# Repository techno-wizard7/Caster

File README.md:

# Caster
Smartwatch-esqe remote controller and communicator

This device is made to be in many ways, an arduino-based custom wrist mounted version of the Flipper-Zero with built-in LoRa, with a few key differences TBD in development. Additionally there will be a default loRa messaging app, based on Bobricus's [Armachat](https://github.com/bobricius/armachat). 

This project is still deep in alpha, and is subject to change rapidly. Contributions not accepted at this time.

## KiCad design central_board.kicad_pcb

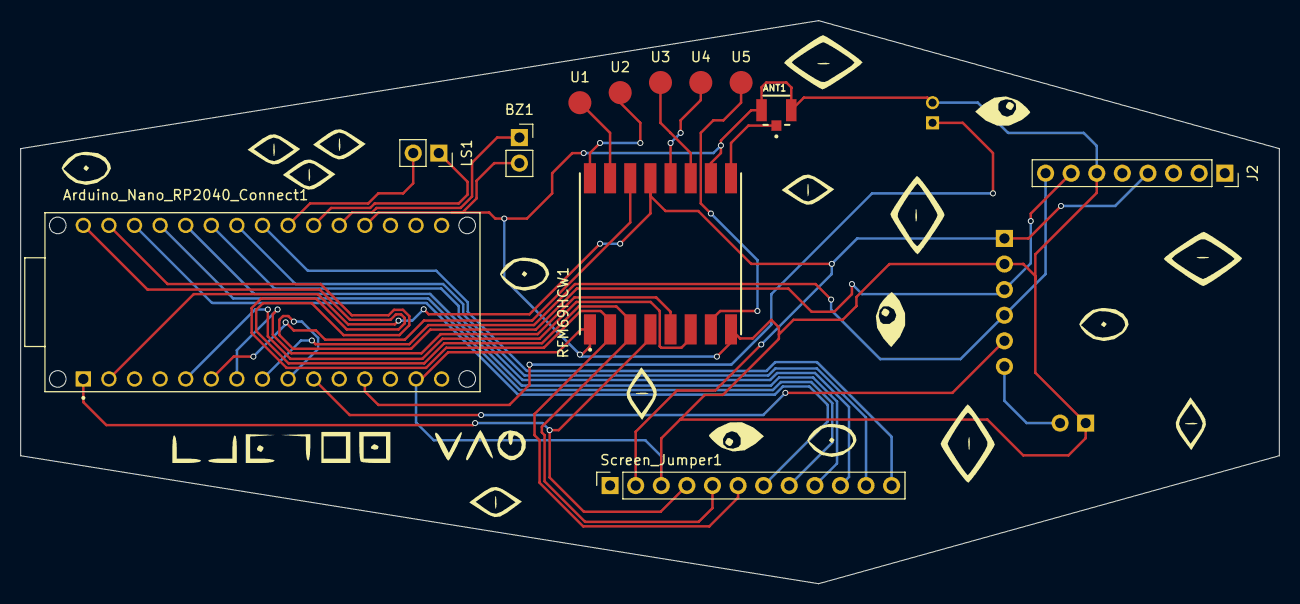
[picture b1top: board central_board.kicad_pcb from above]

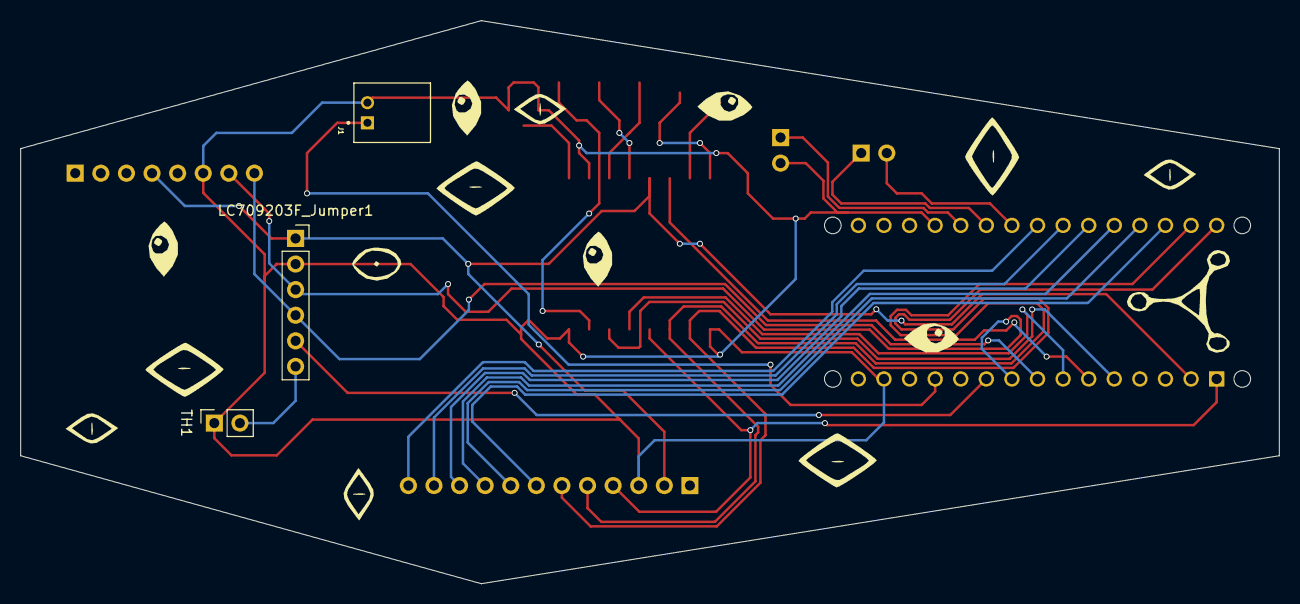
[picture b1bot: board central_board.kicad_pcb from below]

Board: 2 copper layers, 124.9 x 55.9 mm, 15 parts (3 on the bottom side), 23 nets.

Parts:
ANT1: RSP-122811-01; SAMTEC_RSP-122811-01
Arduino_Nano_RP2040_Connect1: ABX00053; MODULE_ABX00053
BZ1: Buzzer; PinSocket_1x02_P2.54mm_Vertical
J1: S2B-PH-K-S(LF)(SN); JST_S2B-PH-K-S(LF)(SN)
J2: Conn_01x08_Male; PinSocket_1x08_P2.54mm_Vertical
LC709203F_Jumper1: Conn_01x06; PinSocket_1x06_P2.54mm_Vertical
LS1: Speaker; PinSocket_1x02_P2.54mm_Vertical
RFM69HCW1: COM-13909; MOD_COM-13909
Screen_Jumper1: Conn_01x12; PinSocket_1x12_P2.54mm_Vertical
TH1: Thermistor; PinSocket_1x02_P2.54mm_Vertical
U1, U2, U3, U4, U5: Single_Jumper; JUMPERPAD

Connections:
+3V3: Arduino_Nano_RP2040_Connect1.2 (+3V3), J2.4, LC709203F_Jumper1.1, RFM69HCW1.13 (3.3V), Screen_Jumper1.2
AUD_OUT: Arduino_Nano_RP2040_Connect1.22 (D4/GPIO26), LS1.2
Aud_IN: Arduino_Nano_RP2040_Connect1.21 (D3/GPIO15), LS1.1
BUZZ: Arduino_Nano_RP2040_Connect1.20 (D2/GPIO25), BZ1.1 (-)
Bat_INT: Arduino_Nano_RP2040_Connect1.10 (A6), LC709203F_Jumper1.5
CIPO: Arduino_Nano_RP2040_Connect1.30 (D12/GPIO4/CIPO), RFM69HCW1.2 (MISO), Screen_Jumper1.6
COPI: Arduino_Nano_RP2040_Connect1.29 (D11/GPIO7/COPI), RFM69HCW1.3 (MOSI), Screen_Jumper1.5
DC: Arduino_Nano_RP2040_Connect1.26 (D8/GPIO20), Screen_Jumper1.9
GND: ANT1.G1, ANT1.G2, Arduino_Nano_RP2040_Connect1.14 (GND), Arduino_Nano_RP2040_Connect1.19 (GND), BZ1.2 (+), J1.2, J2.6, LC709203F_Jumper1.2, RFM69HCW1.1 (GND), RFM69HCW1.8 (GND), RFM69HCW1.10 (GND), Screen_Jumper1.3, TH1.1
LORA_CS: Arduino_Nano_RP2040_Connect1.7 (A3/GPIO29), RFM69HCW1.5 (NSS)
LORA_INT: Arduino_Nano_RP2040_Connect1.6 (A2/GPIO28), RFM69HCW1.14 (DIO0)
Lite: Arduino_Nano_RP2040_Connect1.24 (D6/GPIO18), Screen_Jumper1.11
Lora_RST: Arduino_Nano_RP2040_Connect1.5 (A1/GPIO27), RFM69HCW1.6 (RESET)
unnamed: ANT1.1, RFM69HCW1.9 (ANT)
unnamed: Arduino_Nano_RP2040_Connect1.12 (+5V), J1.1
unnamed: LC709203F_Jumper1.6, TH1.2
RST: Arduino_Nano_RP2040_Connect1.27 (D9/GPIO21), Screen_Jumper1.8
SCK: Arduino_Nano_RP2040_Connect1.1 (D13/GPIO6), RFM69HCW1.4 (SCK), Screen_Jumper1.4
SCL: Arduino_Nano_RP2040_Connect1.9 (A5/GPIO13), J2.7, LC709203F_Jumper1.3
SDA: Arduino_Nano_RP2040_Connect1.8 (A4/GPIO12), J2.8, LC709203F_Jumper1.4
SDCS: Arduino_Nano_RP2040_Connect1.25 (D7/GPIO19), Screen_Jumper1.10
TE: Arduino_Nano_RP2040_Connect1.23 (D5/GPIO17), Screen_Jumper1.12
TFTCS: Arduino_Nano_RP2040_Connect1.28 (D10/GPIO5), Screen_Jumper1.7

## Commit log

2024-06-05 Create test
2024-06-05 Rename central_board.kicad_pcb to pcbs/central_board.kicad_pcb
2024-06-05 Rename central_board.kicad_pro to pcbs/central_board.kicad_pro
2024-06-05 Rename central_board.kicad_sch to pcbs/central_board.kicad_sch
2024-09-02 Added initial (prototype) of firmware. Tested on Uno, but currently compiler-error free on breadboard. Dither graphic primitives and basic screen window functions built (mostly), but have not been co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
2024-09-02 Delete Caster-Src
    removed misplaced link
2024-09-03 collected basic home screen, idle timeout, and wake on activity. rough clock functionality included, but incomplete.

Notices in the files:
central_board.kicad_pcb:
creativecommons.org/licenses/by-nc/4.0
License: CC BY-NC 4.0
